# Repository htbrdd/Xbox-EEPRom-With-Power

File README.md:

# Xbox-EEPRom-With-Power
xbox eeprom reader circuit board

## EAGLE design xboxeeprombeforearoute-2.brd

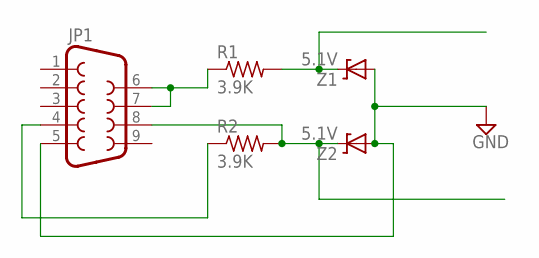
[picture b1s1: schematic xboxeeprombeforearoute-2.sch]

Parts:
JP1: DB9FEMALE; DB9
R1, R2: 3.9K; 0207/9
Z1, Z2: 5.1V; DIODE-ZENER

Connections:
GND: JP1.5, Z1.P$2 (A), Z2.P$2 (A)
unnamed: JP1.6, JP1.7, R1.1
unnamed: JP1.4, R2.1
SCL: R1.2, Z1.P$1 (C)
SDA: JP1.8, R2.2, Z2.P$1 (C)

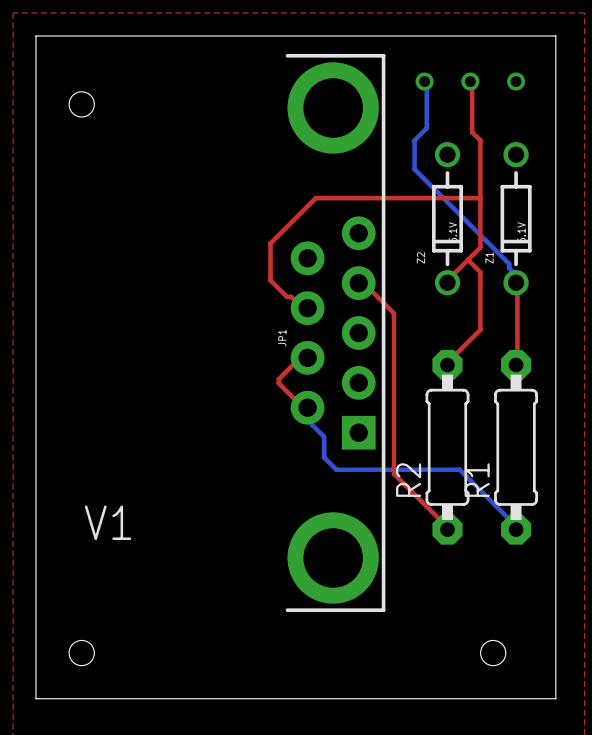
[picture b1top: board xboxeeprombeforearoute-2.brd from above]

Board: 2 copper layers, 28.9 x 36.8 mm, 5 parts (0 on the bottom side), 5 nets.

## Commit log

2016-11-18 :circus_tent: Added .gitattributes & .gitignore files
2016-11-18 Xbox eeprom reader
    inital upload
2016-11-18 readme
2016-11-18 xbox eeprom files

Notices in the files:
parts and their libraries:
SparkFun-Connectors: Licensing: Creative Commons ShareAlike 4.0 International - https://creativecommons.org/licenses/by-sa/4.0
